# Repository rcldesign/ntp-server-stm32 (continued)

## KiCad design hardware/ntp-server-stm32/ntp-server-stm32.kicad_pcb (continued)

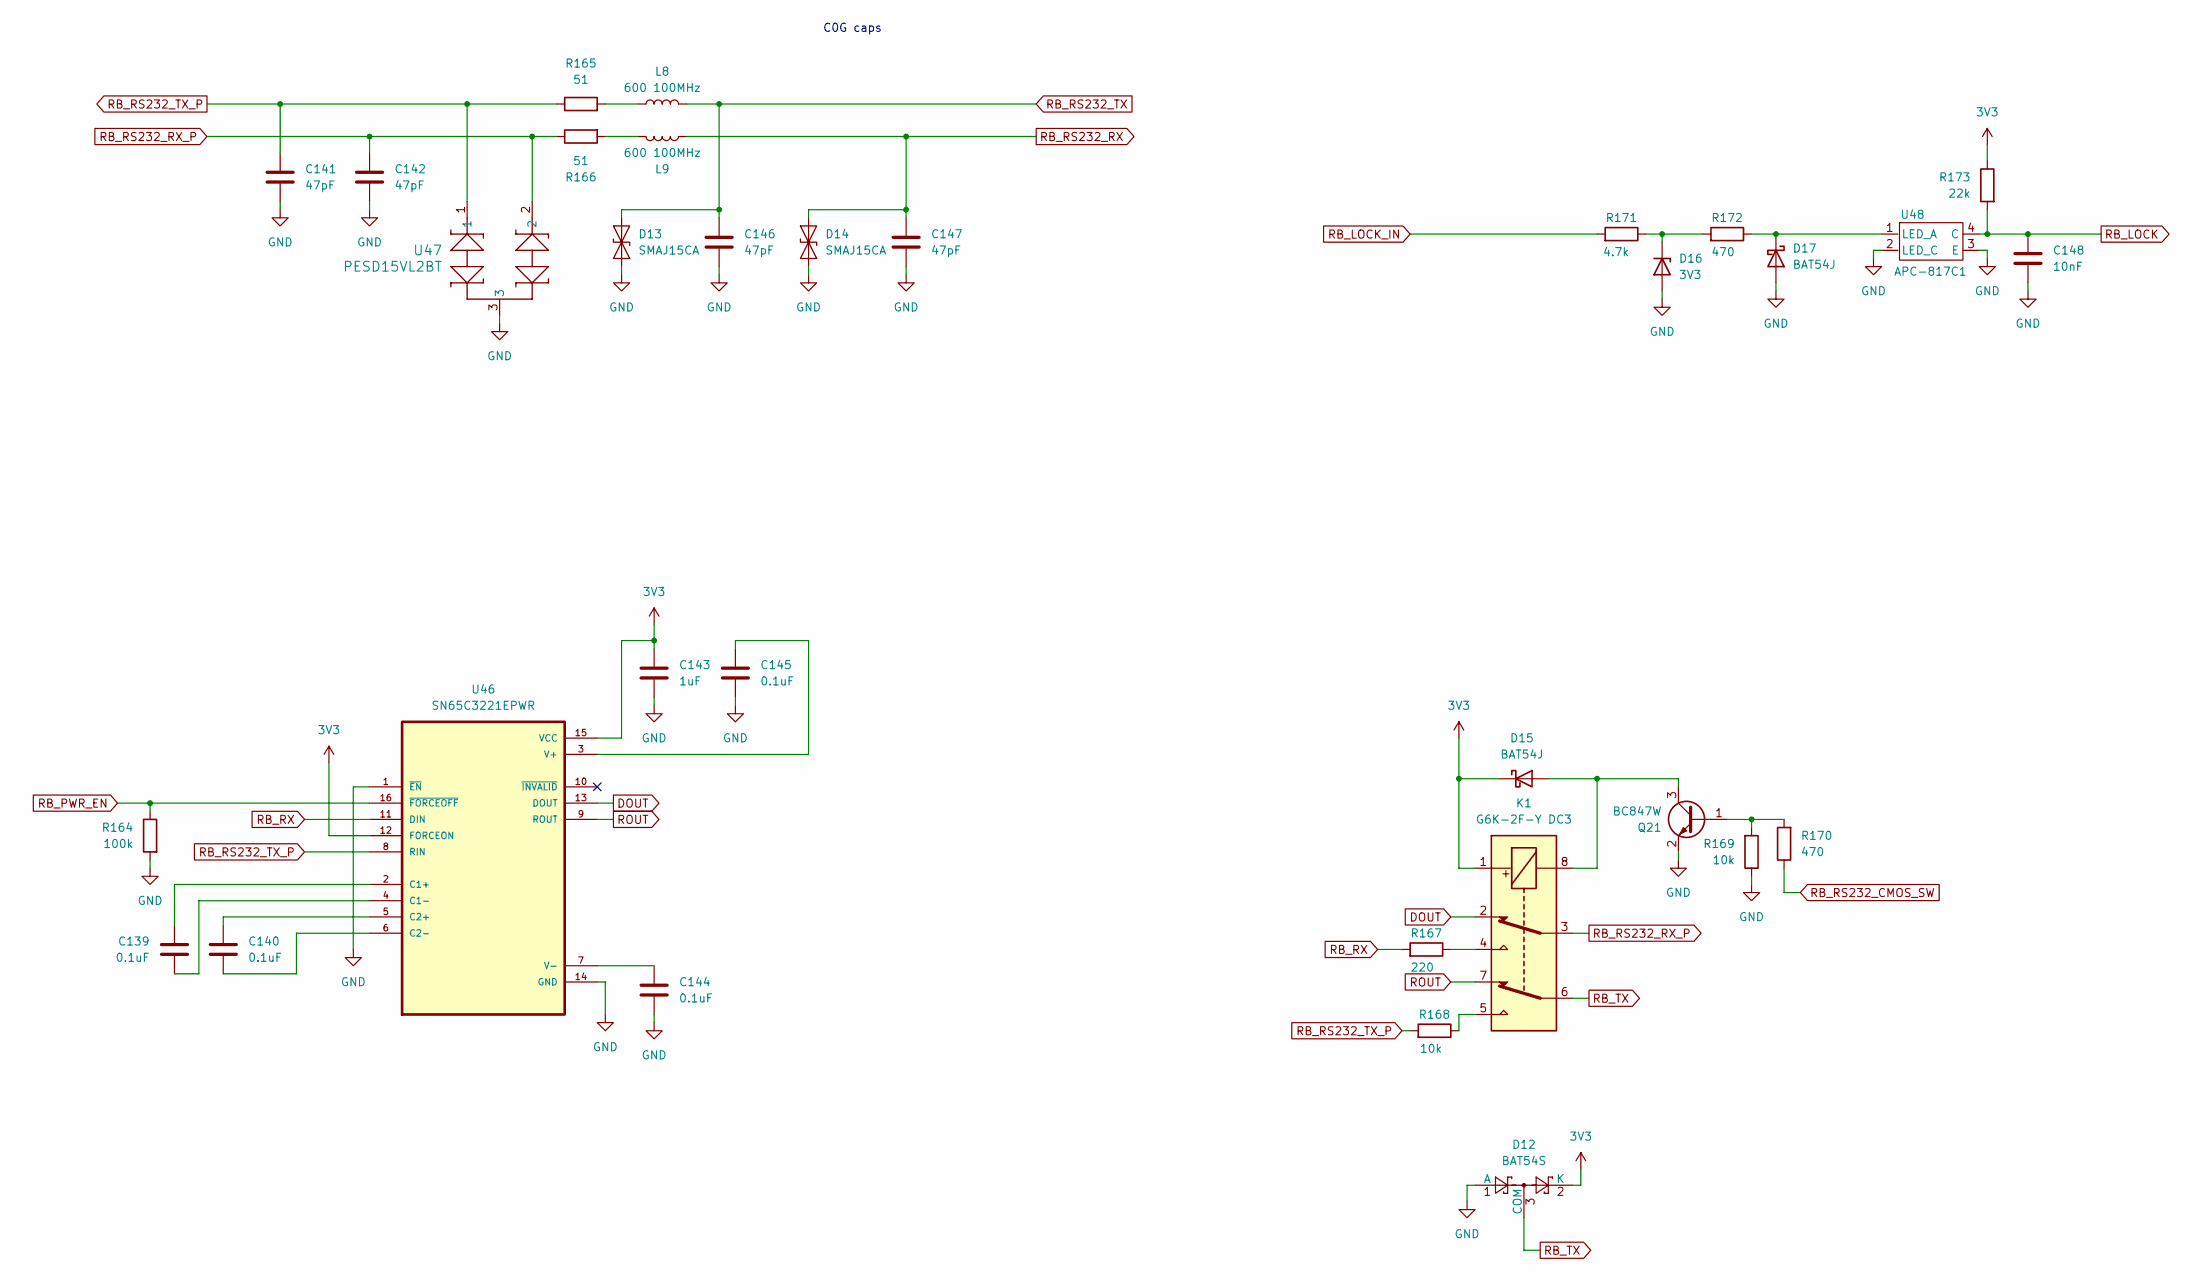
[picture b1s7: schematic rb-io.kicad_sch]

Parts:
C139, C140, C144, C145: 0.1uF; C_0402_1005Metric; TOLERANCE 10%; VOLTAGE 16V; MANUFACTURER_PART_NUMBER GCM155R71C104KA55D; DIGIKEY_PART_NUMBER 490-4759-1-ND
C141, C142, C146, C147: 47pF; C_0402_1005Metric; TOLERANCE 5%; VOLTAGE 50V; MANUFACTURER_PART_NUMBER GCM1555C1H470FA16D; DIGIKEY_PART_NUMBER 490-16445-1-ND
C143: 1uF; C_0603_1608Metric; TOLERANCE 10%; VOLTAGE 16V; MANUFACTURER_PART_NUMBER C0603C105K4RACAUTO; DIGIKEY_PART_NUMBER 399-17704-1-ND
C148: 10nF; C_0402_1005Metric; TOLERANCE 10%; VOLTAGE 16V; MANUFACTURER_PART_NUMBER GRT155R71C103KE01J; DIGIKEY_PART_NUMBER 490-GRT155R71C103KE01JCT-ND
D12: BAT54S; SOT-23-3; MANUFACTURER_PART_NUMBER BAT54S; DIGIKEY_PART_NUMBER 4878-BAT54SCT-ND
D13, D14: SMAJ15CA; DO-214AC; MANUFACTURER_PART_NUMBER SMAJ15CA; DIGIKEY_PART_NUMBER 732-SMAJ15CATR-ND
D15, D17: BAT54J; D_SOD-323F; MANUFACTURER_PART_NUMBER BAT54J-QX; DIGIKEY_PART_NUMBER 1727-BAT54J-QXCT-ND
D16: 3V3; SOT-23-3; MANUFACTURER_PART_NUMBER BZX84C3V3LT1G; DIGIKEY_PART_NUMBER BZX84C3V3LT1GOSCT-ND
K1: G6K-2F-Y DC3; MANUFACTURER_PART_NUMBER G6K-2F-Y DC3; DIGIKEY_PART_NUMBER 39-G6K-2F-YDC3-ND
L8, L9: 600 100MHz; L_0805_2012Metric; MANUFACTURER_PART_NUMBER 2508056017Y2; DIGIKEY_PART_NUMBER 1934-1487-2-ND
Q21: BC847W; SOT-323_SC-70; MANUFACTURER_PART_NUMBER BC847W,135; DIGIKEY_PART_NUMBER 1727-BC847W,135CT-ND
R164: 100k; R_0402_1005Metric; TOLERANCE 1%; MANUFACTURER_PART_NUMBER ERJ-2RKF1003X; DIGIKEY_PART_NUMBER P100KLCT-ND
R165, R166: 51; R_0402_1005Metric; TOLERANCE 1%; MANUFACTURER_PART_NUMBER ERJ-2RKF51R0X; DIGIKEY_PART_NUMBER P51.0LCT-ND
R167: 220; R_0402_1005Metric; TOLERANCE 1%; MANUFACTURER_PART_NUMBER ERJ-2RKF2200X; DIGIKEY_PART_NUMBER P220LCT-ND
R168, R169: 10k; R_0402_1005Metric; TOLERANCE 1%; MANUFACTURER_PART_NUMBER ERJ-2RKF1002X; DIGIKEY_PART_NUMBER P10.0KLCT-ND
R170, R172: 470; R_0402_1005Metric; TOLERANCE 1%; MANUFACTURER_PART_NUMBER ERJ-2RKF4700X; DIGIKEY_PART_NUMBER P470LCT-ND
R171: 4.7k; R_0402_1005Metric; TOLERANCE 1%; MANUFACTURER_PART_NUMBER ERJ-2RKF4701X; DIGIKEY_PART_NUMBER P4.70KLCT-ND
R173: 22k; R_0402_1005Metric; TOLERANCE 1%; MANUFACTURER_PART_NUMBER ERJ-2RKF2202X; DIGIKEY_PART_NUMBER P22.0KLCT-ND
U46: SN65C3221EPWR; SOP65P640X120-16N; MANUFACTURER_PART_NUMBER SN65C3221EPWR; DIGIKEY_PART_NUMBER 296-20992-1-ND
U47: PESD15VL2BT; TSOT-23; MANUFACTURER_PART_NUMBER PESD15VL2BT,215; DIGIKEY_PART_NUMBER 1727-3813-1-ND
U48: APC-817C1; APC817C1SL; MANUFACTURER_PART_NUMBER APC-817C1-SL; DIGIKEY_PART_NUMBER 2007-APC-817C1-SLCT-ND

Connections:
3V3: C143.1, D12.2 (K), D15.1 (K), K1.1, R173.1, U46.12 (FORCEON), U46.15 (VCC); also elsewhere on the board
DOUT: K1.2, U46.13 (DOUT)
GND: C141.2, C142.2, C143.2, C144.2, C145.2, C146.2, C147.2, C148.2, D12.1 (A), D13.1 (A1), D14.1 (A1), D16.2 (A), D17.2 (A), Q21.2 (E), R164.2, R169.1, U46.1 (~EN), U46.14 (GND), U47.3, U48.2 (LED_C), U48.3 (E); also elsewhere on the board
unnamed: D15.2 (A), K1.8, Q21.3 (C)
unnamed: D16.1 (K), R171.1, R172.2
unnamed: D17.1 (K), R172.1, U48.1 (LED_A)
unnamed: K1.4, R167.1
unnamed: K1.5, R168.1
unnamed: L8.1, R165.2
unnamed: L9.1, R166.2
unnamed: Q21.1 (B), R169.2, R170.2
unnamed: C139.1, U46.2 (C1+)
unnamed: C139.2, U46.4 (C1-)
unnamed: C140.1, U46.5 (C2+)
unnamed: C140.2, U46.6 (C2-)
unnamed: C145.1, U46.3 (V+)
unnamed: C144.1, U46.7 (V-)
RB_LOCK: C148.1, R173.2, U48.4 (C); also elsewhere on the board
RB_LOCK_IN: R171.2; also elsewhere on the board
RB_PWR_EN: R164.1, U46.16 (~FORCEOFF); also elsewhere on the board
RB_RS232_CMOS_SW: R170.1; also elsewhere on the board
RB_RS232_RX: C147.1, D14.2 (A2), L9.2; also elsewhere on the board
RB_RS232_RX_P: C142.1, K1.3, R166.1, U47.2
RB_RS232_TX: C146.1, D13.2 (A2), L8.2; also elsewhere on the board
RB_RS232_TX_P: C141.1, R165.1, R168.2, U46.8 (RIN), U47.1
RB_RX: R167.2, U46.11 (DIN); also elsewhere on the board
RB_TX: D12.3 (COM), K1.6; also elsewhere on the board
ROUT: K1.7, U46.9 (ROUT)

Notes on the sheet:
C0G caps

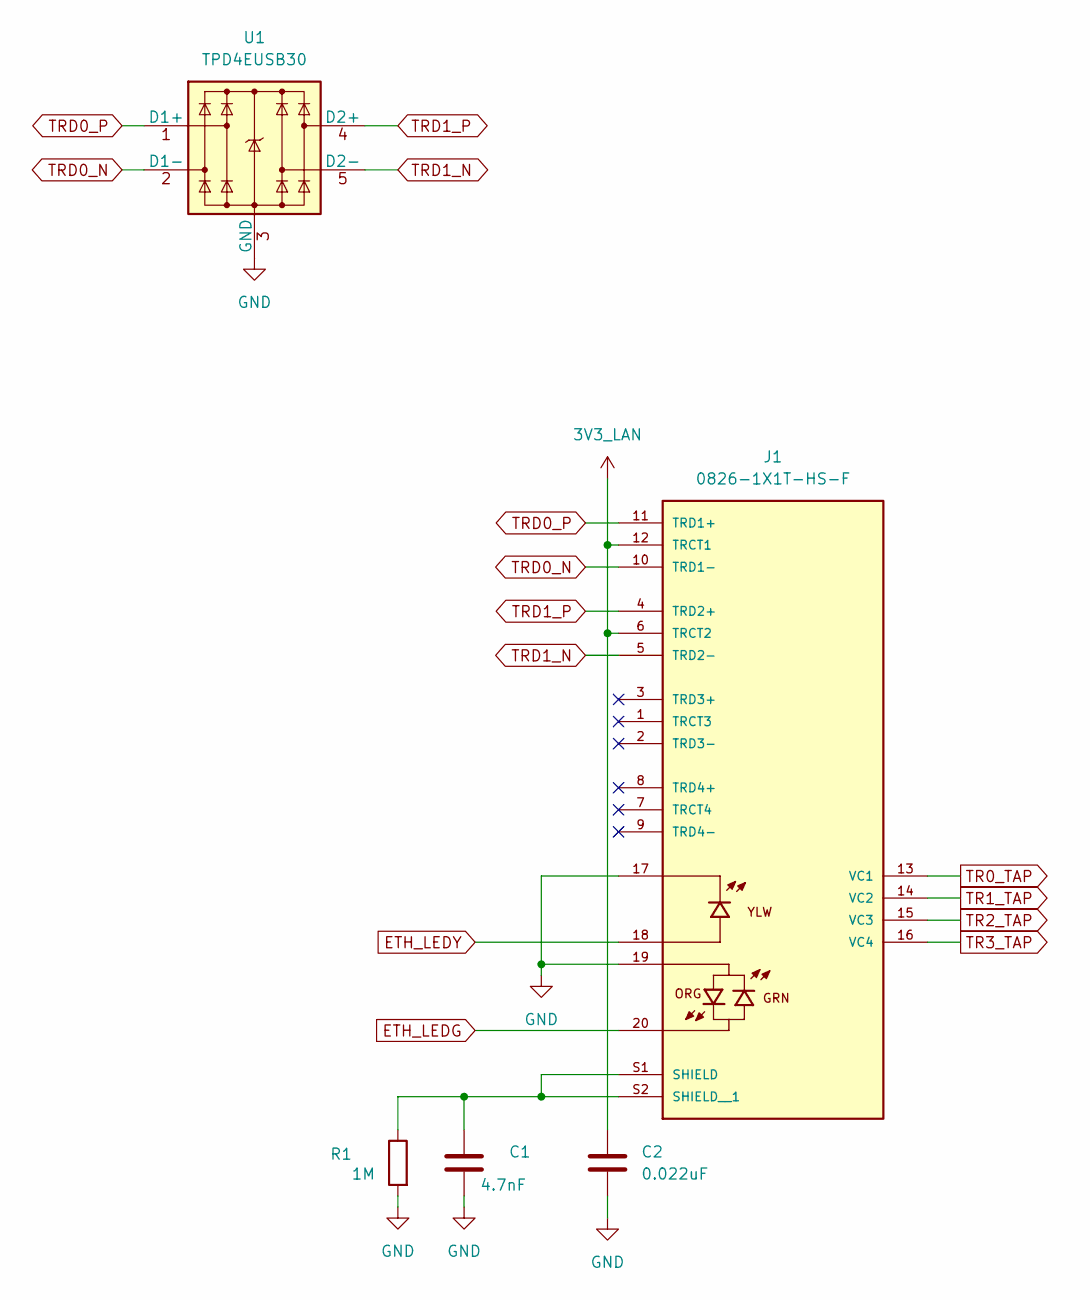
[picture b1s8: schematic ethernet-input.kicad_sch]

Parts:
C1: 4.7nF; C_1812_4532Metric; TOLERANCE 10%; VOLTAGE 2kV; MANUFACTURER_PART_NUMBER C1812C472KGRACAUTO; DIGIKEY_PART_NUMBER 399-16791-1-ND
C2: 0.022uF; C_0402_1005Metric; TOLERANCE 10%; VOLTAGE 50V; MANUFACTURER_PART_NUMBER C0402C223J5RACAUTO; DIGIKEY_PART_NUMBER 399-C0402C223J5RACAUTOCT-ND
J1: 0826-1X1T-HS-F; BEL_0826-1X1T-GH-F; PARTREV D; DIGIKEY_PART_NUMBER 507-2168-ND
R1: 1M; R_0402_1005Metric; TOLERANCE 1%; MANUFACTURER_PART_NUMBER ERJ-2RKF1004X; DIGIKEY_PART_NUMBER P1.00MLCT-ND
U1: TPD4EUSB30; TPD4E02B04DQAR; MANUFACTURER_PART_NUMBER TPD4EUSB30DQAR; DIGIKEY_PART_NUMBER 296-28063-1-ND

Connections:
3V3_LAN: C2.1, J1.6 (TRCT2), J1.12 (TRCT1); also elsewhere on the board
ETH_LEDG: J1.20; also elsewhere on the board
ETH_LEDY: J1.18; also elsewhere on the board
GND: C1.2, C2.2, J1.17, J1.19, R1.2, U1.3 (GND), U1.8 (GND); also elsewhere on the board
unnamed: C1.1, J1.S1 (SHIELD), J1.S2 (SHIELD__1), R1.1
TR0_TAP: J1.13 (VC1); also elsewhere on the board
TR1_TAP: J1.14 (VC2); also elsewhere on the board
TR2_TAP: J1.15 (VC3); also elsewhere on the board
TR3_TAP: J1.16 (VC4); also elsewhere on the board
TRD0_N: J1.10 (TRD1-), U1.2 (D1-), U1.9; also elsewhere on the board
TRD0_P: J1.11 (TRD1+), U1.1 (D1+), U1.10; also elsewhere on the board
TRD1_N: J1.5 (TRD2-), U1.5 (D2-), U1.6; also elsewhere on the board
TRD1_P: J1.4 (TRD2+), U1.4 (D2+), U1.7; also elsewhere on the board

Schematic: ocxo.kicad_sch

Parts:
C98, C99, C101: 0.1uF; C_1210_3225Metric; TOLERANCE 5%; VOLTAGE 16V; MANUFACTURER_PART_NUMBER C1210C104J5GACAUTO; DIGIKEY_PART_NUMBER 399-15804-1-ND
C100, C107, C118: 0.1uF; C_0402_1005Metric; TOLERANCE 10%; VOLTAGE 16V; MANUFACTURER_PART_NUMBER GCM155R71C104KA55D; DIGIKEY_PART_NUMBER 490-4759-1-ND
C102, C103, C104, C105, C111, C112, C113, C114, C115: 10uF; C_1206_3216Metric; TOLERANCE 10%; VOLTAGE 16V; MANUFACTURER_PART_NUMBER CL31B106KOHVPNE; DIGIKEY_PART_NUMBER 1276-6797-1-ND
C106, C110, C116: 10nF; C_0402_1005Metric; TOLERANCE 10%; VOLTAGE 16V; MANUFACTURER_PART_NUMBER GRT155R71C103KE01J; DIGIKEY_PART_NUMBER 490-GRT155R71C103KE01JCT-ND
C108: 4.7nF; C_0402_1005Metric; TOLERANCE 10%; VOLTAGE 16V; MANUFACTURER_PART_NUMBER C0402C472K4RECAUTO; DIGIKEY_PART_NUMBER 399-17875-1-ND
C109, C117: 22uF; C_0805_2012Metric; TOLERANCE 10%; VOLTAGE 16V; MANUFACTURER_PART_NUMBER GRT21BR61C226ME13K; DIGIKEY_PART_NUMBER 490-GRT21BR61C226ME13KCT-ND
D10: BAT54J; D_SOD-323F; MANUFACTURER_PART_NUMBER BAT54J-QX; DIGIKEY_PART_NUMBER 1727-BAT54J-QXCT-ND
L6: 2.2uH; DR73-2R2-R; MANUFACTURER_PART_NUMBER DR73-2R2-R; DIGIKEY_PART_NUMBER 283-DR73-2R2-RTR-ND
R118, R119, R120: 100k; R_0402_1005Metric; TOLERANCE 1%; MANUFACTURER_PART_NUMBER ERJ-2RKF1003X; DIGIKEY_PART_NUMBER P100KLCT-ND
R121: 10M; R_0402_1005Metric; TOLERANCE 1%; MANUFACTURER_PART_NUMBER RK73H1ETTP1005F; DIGIKEY_PART_NUMBER 2019-RK73H1ETTP1005FCT-ND
R122: 1k; R_0402_1005Metric; TOLERANCE 1%; MANUFACTURER_PART_NUMBER ERJ-2RKF1001X; DIGIKEY_PART_NUMBER P1.00KLCT-ND
R123: 22; R_0402_1005Metric; TOLERANCE 1%; MANUFACTURER_PART_NUMBER ERJ-2RKF22R0X; DIGIKEY_PART_NUMBER P22.0LCT-ND
R124, R131: 10k; R_0402_1005Metric; TOLERANCE 1%; MANUFACTURER_PART_NUMBER ERJ-2RKF1002X; DIGIKEY_PART_NUMBER P10.0KLCT-ND
R125: 3.57k; R_0402_1005Metric; TOLERANCE 1%; MANUFACTURER_PART_NUMBER ERJ-2RKF3571X; DIGIKEY_PART_NUMBER P3.57KLCT-ND
R126: 25m; R_1206_3216Metric; TOLERANCE 0.5%; MANUFACTURER_PART_NUMBER WSL1206R0250FEA; DIGIKEY_PART_NUMBER WSLC-.025CT-ND
R127: 12.4k; R_0402_1005Metric; TOLERANCE 1%; MANUFACTURER_PART_NUMBER ERJ-2RKF1242X; DIGIKEY_PART_NUMBER P12.4KLCT-ND
R128: 2.4k; R_0402_1005Metric; TOLERANCE 1%; MANUFACTURER_PART_NUMBER ERJ-2RKF2401X; DIGIKEY_PART_NUMBER P12.4KLCT-ND
R129: 12.1k; R_0603_1608Metric; TOLERANCE 0.1%; MANUFACTURER_PART_NUMBER RQ73C1J12K1BTD; DIGIKEY_PART_NUMBER A140146CT-ND
R130: 3.83k; R_0603_1608Metric; TOLERANCE 0.1%; MANUFACTURER_PART_NUMBER RQ73C1J3K83BTD; DIGIKEY_PART_NUMBER A140873CT-ND
U36: OPA320AIDBVT; SOT95P280X145-5N; MANUFACTURER_PART_NUMBER OPA320AIDBVT; DIGIKEY_PART_NUMBER 296-29510-1-ND
U37: INA228AQDGSRQ1; VSSOP10_DGS_TEX; MANUFACTURER_PART_NUMBER INA228AQDGSRQ1; DIGIKEY_PART_NUMBER 296-INA228AQDGSRQ1CT-ND
U38: AP3441SHE-7B; AP3441SHE-7B_DIO-M; MANUFACTURER_PART_NUMBER AP3441SHE-7B; DIGIKEY_PART_NUMBER AP3441SHE-7BDITR-ND
U39: TPS7A5201QRGRRQ1; RGR20_2P05X2P05_TEX; MANUFACTURER_PART_NUMBER TPS7A5201QRGRRQ1; DIGIKEY_PART_NUMBER 296-50505-1-ND
Y3: OH300; Oscillator_SMD_OCXO_ConnorWinfield_OH300; MANUFACTURER_PART_NUMBER OH300-61003CV-010.0M; DIGIKEY_PART_NUMBER CW752CT-ND

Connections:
3V3: C107.1, R131.1, U37.1 (A1), U37.6 (VS); also elsewhere on the board
5V: C102.1, C103.1, C104.1, U38.3 (VIN); also elsewhere on the board
5V_PSU_PG: U38.7 (EN); also elsewhere on the board
GND: C98.2, C99.2, C100.2, C101.2, C102.2, C103.2, C104.2, C105.2, C106.2, C107.2, C109.2, C111.2, C112.2, C113.2, C114.2, C115.2, C116.2, C117.2, C118.2, R119.1, R124.2, R128.2, R130.2, U36.2 (V-), U37.7 (GND), U38.4 (PGND), U38.8 (SGND), U38.9 (PAD), U39.8 (GND), U39.18 (GND), U39.21 (EPAD), Y3.7 (GND); also elsewhere on the board
I2C_SCL: U37.5 (SCL); also elsewhere on the board
I2C_SDA: U37.2 (A0), U37.4 (SDA); also elsewhere on the board
INA_ALERT_OCXO: U37.3 (ALERT); also elsewhere on the board
unnamed: C99.1, R118.2, R119.2, R121.1
unnamed: C109.1, C110.1, D10.2 (A), R126.2, R129.1, U37.10 (IN+), U39.1 (OUT), U39.19 (OUT), U39.20 (OUT)
unnamed: C108.1, C111.1, C112.1, C113.1, C114.1, C115.1, C117.1, C118.1, D10.1 (K), L6.2, R127.1, U39.12 (BIAS), U39.15 (IN), U39.16 (IN), U39.17 (IN)
unnamed: C98.1, R120.2, R121.2, U36.3 (+IN)
unnamed: R122.1, U36.1 (OUT), U36.4 (-IN)
unnamed: C105.1, C106.1, R126.1, U37.8 (VBUS), U37.9 (IN-), Y3.3 (VCC)
unnamed: C108.2, R127.2, R128.1, U38.1 (FB)
unnamed: L6.1, U38.6 (LX)
unnamed: R125.1, U38.2 (PG)
unnamed: C110.2, R129.2, R130.1, U39.3 (FB)
unnamed: C116.1, U39.13 (NR/SS)
unnamed: R123.1, Y3.4 (OUT)
OCXO_CLK_OUT: R123.2; also elsewhere on the board
OCXO_LDO_PG: R131.2, U39.4 (PG); also elsewhere on the board
OCXO_PSU_PG: R124.1, R125.2, U39.14 (EN); also elsewhere on the board
OCXO_V: C101.1, R122.2, Y3.1 (Vcontrol); also elsewhere on the board
OCXO_VC: R120.1; also elsewhere on the board
VDDA: C100.1, R118.1, U36.5 (V+); also elsewhere on the board

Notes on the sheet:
3.7V ->
<- 3.7V
PG pulled to VIN When power good
I2C Address: 0x46
50-ohm trace

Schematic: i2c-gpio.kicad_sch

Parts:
C161, C162, C163, C164, C165, C166, C167, C187, C202: 0.1uF; C_0402_1005Metric; TOLERANCE 10%; VOLTAGE 16V; MANUFACTURER_PART_NUMBER GCM155R71C104KA55D; DIGIKEY_PART_NUMBER 490-4759-1-ND
C201: 1nF; C_0402_1005Metric; TOLERANCE 5%; VOLTAGE 50V; MANUFACTURER_PART_NUMBER C0402C102J5GECAUTO; DIGIKEY_PART_NUMBER 399-C0402C102J5GECAUTOCT-ND
R190, R191, R192, R193, R194, R195, R196, R220, R221, R222, R223, R224, R225, R226, R227, R236, R254, R265: 10k; R_0402_1005Metric; TOLERANCE 1%; MANUFACTURER_PART_NUMBER ERJ-2RKF1002X; DIGIKEY_PART_NUMBER P10.0KLCT-ND

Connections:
3V3_STM: R190.1, R191.1, R192.1, R193.1, R194.1, R195.1, R196.1, R220.1, R221.1, R222.1, R223.1, R224.1, R225.1, R226.1, R227.1, R236.1, R254.1, R265.1; also elsewhere on the board
BUTTON_1: C161.1, R190.2; also elsewhere on the board
BUTTON_2: C162.1, R191.2; also elsewhere on the board
BUTTON_3: C163.1, R192.2; also elsewhere on the board
BUTTON_4: C164.1, R193.2; also elsewhere on the board
BUTTON_5: C165.1, R194.2; also elsewhere on the board
BUTTON_6: C166.1, R195.2; also elsewhere on the board
BUTTON_7: C167.1, R196.2; also elsewhere on the board
ENC_BUTTON: C187.1, R236.2; also elsewhere on the board
GND: C161.2, C162.2, C163.2, C164.2, C165.2, C166.2, C167.2, C187.2, C201.2, C202.2; also elsewhere on the board
INA_ALERT_3V3: R221.2; also elsewhere on the board
INA_ALERT_3V3_GPS: R224.2; also elsewhere on the board
INA_ALERT_3V3_STM: R222.2; also elsewhere on the board
INA_ALERT_5V_DISP: R223.2; also elsewhere on the board
INA_ALERT_5V_PANEL: R227.2; also elsewhere on the board
INA_ALERT_OCXO: R226.2; also elsewhere on the board
INA_ALERT_VCC_RB: R265.2; also elsewhere on the board
INA_ALERT_V_ANT: R225.2; also elsewhere on the board
INA_ALERT_V_POE: R220.2; also elsewhere on the board
PROX_WAKE: C202.1, R254.2; also elsewhere on the board
RTC_TAMPER: C201.1; also elsewhere on the board

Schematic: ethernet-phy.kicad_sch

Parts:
C13: 4.7uF; C_0805_2012Metric; TOLERANCE 10%; VOLTAGE 16V; MANUFACTURER_PART_NUMBER GRT21BR71C475KE13K; DIGIKEY_PART_NUMBER 490-GRT21BR71C475KE13KCT-ND
C14, C16: 27pF; C_0402_1005Metric; TOLERANCE 5%; VOLTAGE 50V; MANUFACTURER_PART_NUMBER GCM1555C1H270JA16D; DIGIKEY_PART_NUMBER 490-12651-1-ND
C15, C19, C20: 0.1uF; C_0402_1005Metric; TOLERANCE 10%; VOLTAGE 16V; MANUFACTURER_PART_NUMBER GCM155R71C104KA55D; DIGIKEY_PART_NUMBER 490-4759-1-ND
C17: 470pF; C_0402_1005Metric; TOLERANCE 5%; VOLTAGE 50V; MANUFACTURER_PART_NUMBER GCM1555C1H471FA16D; DIGIKEY_PART_NUMBER 490-GCM1555C1H471FA16DCT-ND
C18: 1uF; C_0603_1608Metric; TOLERANCE 10%; VOLTAGE 16V; MANUFACTURER_PART_NUMBER C0603C105K4RACAUTO; DIGIKEY_PART_NUMBER 399-17704-1-ND
FB1: 600; 1206; MANUFACTURER_PART_NUMBER BLM31PG601SN1L; DIGIKEY_PART_NUMBER 490-16533-1-ND
R31, R32, R33, R34: 100; R_0402_1005Metric; TOLERANCE 1%; MANUFACTURER_PART_NUMBER ERJ-2RKF1000X; DIGIKEY_PART_NUMBER P100LCT-ND
R35: 10k; R_0402_1005Metric; TOLERANCE 1%; MANUFACTURER_PART_NUMBER ERJ-2RKF1002X; DIGIKEY_PART_NUMBER P10.0KLCT-ND
R36: 1.5k; R_0402_1005Metric; TOLERANCE 1%; MANUFACTURER_PART_NUMBER ERJ-2RKF1501X; DIGIKEY_PART_NUMBER P1.50KLCT-ND
R37: 12.1k; R_0402_1005Metric; TOLERANCE 1%; MANUFACTURER_PART_NUMBER ERJ-2RKF1212X; DIGIKEY_PART_NUMBER P12.1KLCT-ND
R38, R39: 330; R_0402_1005Metric; TOLERANCE 1%; MANUFACTURER_PART_NUMBER ERJ-2RKF3300X; DIGIKEY_PART_NUMBER P330LCT-ND
R40, R41: 4.75k; R_0402_1005Metric; TOLERANCE 1%; MANUFACTURER_PART_NUMBER RK73H1ERTTP4751F; DIGIKEY_PART_NUMBER 2019-RK73H1ERTTP4751FCT-ND
R42, R43, R44, R45: 49.9; R_0402_1005Metric; TOLERANCE 1%; MANUFACTURER_PART_NUMBER ERJ-2RKF49R9X; DIGIKEY_PART_NUMBER P49.9LCT-ND
R49, R228, R229, R230: 4.99k; R_0402_1005Metric; TOLERANCE 1%; MANUFACTURER_PART_NUMBER ERJ-2RKF4991X; DIGIKEY_PART_NUMBER P4.99KLCT-ND
U11: LAN8742AI-CZ-TR; QFN50P400X400X100-25N; MANUFACTURER_PART_NUMBER LAN8742AI-CZ-TR; DIGIKEY_PART_NUMBER LAN8742AI-CZ-CT-ND
Y1: 25MHz; 445I23E25M00000; MANUFACTURER_PART_NUMBER 445I23E25M00000; DIGIKEY_PART_NUMBER 110-445I23E25M00000CT-ND

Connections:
3V3: C15.1, FB1.2, U11.9 (VDDIO); also elsewhere on the board
3V3_LAN: C13.1, C19.1, C20.1, FB1.1, R36.1, R42.1, R43.1, R44.1, R45.1, R49.1, R228.1, R229.1, U11.1 (VDD2A), U11.19 (VDD1A); also elsewhere on the board
ETH_LEDG: R38.2, R40.1; also elsewhere on the board
ETH_LEDY: R39.2, R41.1; also elsewhere on the board
GND: C13.2, C14.2, C15.2, C16.2, C17.2, C18.2, C19.2, C20.2, R35.2, R37.2, R40.2, R41.2, R230.2, U11.25 (VSS); also elsewhere on the board
LAN_RST_N: R35.1, U11.15 (~RST); also elsewhere on the board
unnamed: R33.2, R229.2, U11.11 (CRS_DV/MODE2)
unnamed: R38.1, U11.3 (LED1/~INT/~PME/REGOFF)
unnamed: R39.1, U11.2 (LED2/~INT/~PME/~INTSEL)
unnamed: R37.1, U11.24 (RBIAS)
unnamed: R31.2, R49.2, U11.8 (RXD0/MODE0)
unnamed: R32.2, R228.2, U11.7 (RXD1/MODE1)
unnamed: R34.2, R230.1, U11.10 (RXER/PHYAD0)
unnamed: C17.1, C18.1, U11.6 (VDDCR)
unnamed: C16.1, U11.5 (XTAL1/CLKIN), Y1.2
unnamed: C14.1, U11.4 (XTAL2), Y1.1
RMII_CRS_DV: R33.1; also elsewhere on the board
RMII_MDC: U11.13 (MDC); also elsewhere on the board
RMII_MDIO: R36.2, U11.12 (MDIO); also elsewhere on the board
RMII_REF_CLK: U11.14 (~INT/REFCLKO); also elsewhere on the board
RMII_RXD0: R31.1; also elsewhere on the board
RMII_RXD1: R32.1; also elsewhere on the board
RMII_RXER: R34.1; also elsewhere on the board
RMII_TXD0: U11.17 (TXD0); also elsewhere on the board
RMII_TXD1: U11.18 (TXD1); also elsewhere on the board
RMII_TX_EN: U11.16 (TXEN); also elsewhere on the board
TRD0_N: R44.2, U11.20 (TXN); also elsewhere on the board
TRD0_P: R45.2, U11.21 (TXP); also elsewhere on the board
TRD1_N: R42.2, U11.22 (RXN); also elsewhere on the board
TRD1_P: R43.2, U11.23 (RXP); also elsewhere on the board

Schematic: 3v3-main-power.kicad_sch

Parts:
C63: 10nF; C_0402_1005Metric; TOLERANCE 10%; VOLTAGE 16V; MANUFACTURER_PART_NUMBER GRT155R71C103KE01J; DIGIKEY_PART_NUMBER 490-GRT155R71C103KE01JCT-ND
C64, C65, C66, C73, C74, C76, C78: 10uF; C_1206_3216Metric; TOLERANCE 10%; VOLTAGE 16V; MANUFACTURER_PART_NUMBER CL31B106KOHVPNE; DIGIKEY_PART_NUMBER 1276-6797-1-ND
C67, C68, C83, C86, C87: 0.1uF; C_0402_1005Metric; TOLERANCE 10%; VOLTAGE 16V; MANUFACTURER_PART_NUMBER GCM155R71C104KA55D; DIGIKEY_PART_NUMBER 490-4759-1-ND
C69, C70: 4.7nF; C_0402_1005Metric; TOLERANCE 10%; VOLTAGE 16V; MANUFACTURER_PART_NUMBER C0402C472K4RECAUTO; DIGIKEY_PART_NUMBER 399-17875-1-ND
C71, C72: 47uF; C_1210_3225Metric; TOLERANCE 10%; VOLTAGE 16V; MANUFACTURER_PART_NUMBER GRT32EC81C476KE13L; DIGIKEY_PART_NUMBER 490-12494-1-ND
C75, C77, C80: 2.2uF; C_2220_5750Metric; TOLERANCE 10%; VOLTAGE 100V; MANUFACTURER_PART_NUMBER CGA9P3X7T2E225K250KA; DIGIKEY_PART_NUMBER 445-7950-1-ND
C79: 1uF; C_0805_2012Metric; TOLERANCE 10%; VOLTAGE 100V; MANUFACTURER_PART_NUMBER 08051C105K4T2A; DIGIKEY_PART_NUMBER 478-KAM21KR72A105KUCT-ND
C81: 4.7uF; C_0805_2012Metric; TOLERANCE 10%; VOLTAGE 16V; MANUFACTURER_PART_NUMBER GRT21BR71C475KE13K; DIGIKEY_PART_NUMBER 490-GRT21BR71C475KE13KCT-ND
C82: 2.2uF; C_0805_2012Metric; TOLERANCE 10%; VOLTAGE 16V; MANUFACTURER_PART_NUMBER GRT21BR71C225KE01L; DIGIKEY_PART_NUMBER 490-GRT21BR71C225KE01LCT-ND
C84, C85: 1uF; C_0603_1608Metric; TOLERANCE 10%; VOLTAGE 16V; MANUFACTURER_PART_NUMBER C0603C105K4RACAUTO; DIGIKEY_PART_NUMBER 399-17704-1-ND
FB7: 600; 1206; MANUFACTURER_PART_NUMBER BLM31PG601SN1L; DIGIKEY_PART_NUMBER 490-16533-1-ND
L2: 6.8uH; SRP1265A-6R8M; MANUFACTURER_PART_NUMBER SRP1265A-6R8M; DIGIKEY_PART_NUMBER SRP1265A-6R8MTR-ND
L3: 2.2uH; DR73-2R2-R; MANUFACTURER_PART_NUMBER DR73-2R2-R; DIGIKEY_PART_NUMBER 283-DR73-2R2-RTR-ND
R90: 200k; R_0402_1005Metric; TOLERANCE 1%; MANUFACTURER_PART_NUMBER ERJ-2RKF2003X; DIGIKEY_PART_NUMBER P200KLCT-ND
R91: 100k; R_0402_1005Metric; TOLERANCE 1%; MANUFACTURER_PART_NUMBER ERJ-2RKF1003X; DIGIKEY_PART_NUMBER P100KLCT-ND
R92, R95, R99, R104, R105: 10k; R_0402_1005Metric; TOLERANCE 1%; MANUFACTURER_PART_NUMBER ERJ-2RKF1002X; DIGIKEY_PART_NUMBER P10.0KLCT-ND
R93: 2.21k; R_0402_1005Metric; TOLERANCE 1%; MANUFACTURER_PART_NUMBER ERJ-2RKF2211X; DIGIKEY_PART_NUMBER P2.21KLCT-ND
R94: 6.81k; R_0402_1005Metric; TOLERANCE 1%; MANUFACTURER_PART_NUMBER ERJ-2RKF6811X; DIGIKEY_PART_NUMBER P6.81KLTR-ND
R96: 24.9k; R_0402_1005Metric; TOLERANCE 1%; MANUFACTURER_PART_NUMBER ERJ-2RKF2492X; DIGIKEY_PART_NUMBER P24.9KLCT-ND
R97: 15k; R_0402_1005Metric; TOLERANCE 1%; MANUFACTURER_PART_NUMBER RK73H1ETTP1502F; DIGIKEY_PART_NUMBER 2019-RK73H1ETTP1502FCT-ND
R98: 2.05k; R_0402_1005Metric; TOLERANCE 1%; MANUFACTURER_PART_NUMBER ERJ-2RKF2051X; DIGIKEY_PART_NUMBER P2.05KLTR-ND
R100: 2.2k; R_0402_1005Metric; TOLERANCE 1%; MANUFACTURER_PART_NUMBER ERJ-2RKF2201X; DIGIKEY_PART_NUMBER P2.20KLCT-ND
R101, R103: 2.2; R_0402_1005Metric; TOLERANCE 1%; MANUFACTURER_PART_NUMBER ERJ-U02F2R20X; DIGIKEY_PART_NUMBER 10-ERJ-U02F2R20XTR-ND
R102: 50m; R_1206_3216Metric; TOLERANCE 0.5%; MANUFACTURER_PART_NUMBER WSL1206R0500FEA; DIGIKEY_PART_NUMBER WSLC-.05CT-ND
R106, R107: 100m; R_1206_3216Metric; TOLERANCE 0.5%; MANUFACTURER_PART_NUMBER WSL1206R1000FEA; DIGIKEY_PART_NUMBER WSLC-.10CT-ND
U28: MIC28516T-E/PHA; MIC28516T-EPHA; MANUFACTURER_PART_NUMBER MIC28516T-E/PHA; DIGIKEY_PART_NUMBER 150-MIC28516T-E/PHATR-ND
U29: AP3441SHE-7B; AP3441SHE-7B_DIO-M; MANUFACTURER_PART_NUMBER AP3441SHE-7B; DIGIKEY_PART_NUMBER AP3441SHE-7BDITR-ND
U30, U31, U32: INA228AQDGSRQ1; VSSOP10_DGS_TEX; MANUFACTURER_PART_NUMBER INA228AQDGSRQ1; DIGIKEY_PART_NUMBER 296-INA228AQDGSRQ1CT-ND
U33: RT9742VGJ5; TSOT-23-5; MANUFACTURER_PART_NUMBER RT9742VGJ5; DIGIKEY_PART_NUMBER 1028-RT9742VGJ5TR-ND

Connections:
3V3: C83.1, C86.1, C87.1, R102.2, R106.1, U30.6 (VS), U30.8 (VBUS), U30.9 (IN-), U31.2 (A0), U31.6 (VS), U31.10 (IN+), U32.6 (VS); also elsewhere on the board
3V3_PSU_PG: R92.1, R94.2; also elsewhere on the board
3V3_STM: R105.1, R106.2, U31.8 (VBUS), U31.9 (IN-); also elsewhere on the board
5V: C64.1, C65.1, C66.1, C69.1, C71.1, C72.1, C84.1, L2.2, R95.1, R97.1, U29.3 (VIN), U33.5 (IN); also elsewhere on the board
5V_DISP: FB7.2; also elsewhere on the board
5V_PSU_PG: R95.2, U28.32 (PG), U29.7 (EN); also elsewhere on the board
DISP_EN: R104.1, U33.4 (EN); also elsewhere on the board
GND: C63.2, C64.2, C65.2, C66.2, C71.2, C72.2, C73.2, C74.2, C75.2, C76.2, C77.2, C78.2, C79.2, C80.2, C81.2, C82.2, C83.2, C84.2, C85.2, C86.2, C87.2, R91.2, R92.2, R98.2, R100.2, R104.2, U28.2 (PGND), U28.16 (PGND), U28.17 (PGND), U28.18 (PGND), U28.19 (PGND), U28.22 (PGND), U28.23 (EXTVDD), U28.28 (AGND), U28.29 (PGND), U28.33 (PGND), U29.4 (PGND), U29.8 (SGND), U29.9 (PAD), U30.1 (A1), U30.7 (GND), U31.1 (A1), U31.7 (GND), U32.1 (A1), U32.7 (GND), U33.2 (GND); also elsewhere on the board
I2C_SCL: U30.2 (A0), U30.5 (SCL), U31.5 (SCL), U32.5 (SCL); also elsewhere on the board
I2C_SDA: U30.4 (SDA), U31.4 (SDA), U32.2 (A0), U32.4 (SDA); also elsewhere on the board
INA_ALERT_3V3: U30.3 (ALERT); also elsewhere on the board
INA_ALERT_3V3_STM: U31.3 (ALERT); also elsewhere on the board
INA_ALERT_5V_DISP: U32.3 (ALERT); also elsewhere on the board
unnamed: C67.1, R96.2
unnamed: C68.2, L2.1, R93.2, R96.1, U28.3 (SW), U28.12 (SW), U28.13 (SW), U28.14 (SW), U28.15 (SW), U28.20 (SW)
unnamed: C68.1, U28.4 (BST)
unnamed: C67.2, C69.2, R97.2, R98.1, U28.27 (FB)
unnamed: R90.2, R91.1, U28.25 (FREQ)
unnamed: R93.1, U28.1 (ILIM)
unnamed: C63.1, U28.26 (SS)
unnamed: C81.1, R103.1, U28.21 (PVDD)
unnamed: C79.1, R101.2, U28.31 (SVIN)
unnamed: C82.1, R103.2, U28.30 (VDD)
unnamed: C70.2, R99.2, R100.1, U29.1 (FB)
unnamed: L3.1, U29.6 (LX)
unnamed: R94.1, U29.2 (PG)
unnamed: C70.1, C73.1, C74.1, C76.1, C78.1, L3.2, R99.1, R102.1, U30.10 (IN+)
unnamed: C85.1, R107.1, U32.10 (IN+), U33.1 (OUT)
unnamed: FB7.1, R107.2, U32.8 (VBUS), U32.9 (IN-)
POE_PG: U28.24 (EN); also elsewhere on the board
V_DISP_EN_FAULT: R105.2, U33.3 (nFLG); also elsewhere on the board
V_POE: C75.1, C77.1, C80.1, R90.1, R101.1, U28.5 (PVIN), U28.6 (PVIN), U28.7 (PVIN), U28.8 (PVIN), U28.9 (PVIN), U28.10 (PVIN), U28.11 (PVIN); also elsewhere on the board

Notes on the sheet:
I2C Address: 0x41
1.9A Maximum ->
PG pulled to VIN When power good
I2C Address: 0x42
I2C Address: 0x43
8A Maximum ->

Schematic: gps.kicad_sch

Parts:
C45, C47: 1uF; C_0603_1608Metric; TOLERANCE 10%; VOLTAGE 16V; MANUFACTURER_PART_NUMBER C0603C105K4RACAUTO; DIGIKEY_PART_NUMBER 399-17704-1-ND
C46: 4.7uF; C_0805_2012Metric; TOLERANCE 10%; VOLTAGE 16V; MANUFACTURER_PART_NUMBER GRT21BR71C475KE13K; DIGIKEY_PART_NUMBER 490-GRT21BR71C475KE13KCT-ND
C48, C51: 0.1uF; C_0402_1005Metric; TOLERANCE 10%; VOLTAGE 16V; MANUFACTURER_PART_NUMBER GCM155R71C104KA55D; DIGIKEY_PART_NUMBER 490-4759-1-ND
C49: 0.47uF; C_0603_1608Metric; TOLERANCE 10%; VOLTAGE 16V; MANUFACTURER_PART_NUMBER GRT188R71C474KE01D; DIGIKEY_PART_NUMBER 490-GRT188R71C474KE01DCT-ND
C50: 10uF; C_1206_3216Metric; TOLERANCE 10%; VOLTAGE 16V; MANUFACTURER_PART_NUMBER CL31B106KOHVPNE; DIGIKEY_PART_NUMBER 1276-6797-1-ND
FB3: 600; 1206; MANUFACTURER_PART_NUMBER BLM31PG601SN1L; DIGIKEY_PART_NUMBER 490-16533-1-ND
R69: 100k; R_0402_1005Metric; TOLERANCE 1%; MANUFACTURER_PART_NUMBER ERJ-2RKF1003X; DIGIKEY_PART_NUMBER P100KLCT-ND
R70: 374; R_0402_1005Metric; TOLERANCE 1%; MANUFACTURER_PART_NUMBER ERJ-2RKF3740X; DIGIKEY_PART_NUMBER P374LCT-ND
R71: 33.2k; R_0402_1005Metric; TOLERANCE 1%; MANUFACTURER_PART_NUMBER ERJ-2RKF3322X; DIGIKEY_PART_NUMBER P33.2KLCT-ND
R72: 75m; R_1206_3216Metric; TOLERANCE 0.5%; MANUFACTURER_PART_NUMBER WSL1206R0750FEA; DIGIKEY_PART_NUMBER 541-10064-1-ND
R197: 453k; R_0402_1005Metric; TOLERANCE 1%; MANUFACTURER_PART_NUMBER ERJ-2RKF4533X; DIGIKEY_PART_NUMBER P453KLCT-ND
R214: 49.9k; R_0402_1005Metric; TOLERANCE 1%; MANUFACTURER_PART_NUMBER ERJ-2RKF4992X; DIGIKEY_PART_NUMBER P49.9KLCT-ND
R215: 10k; R_0402_1005Metric; TOLERANCE 1%; MANUFACTURER_PART_NUMBER ERJ-2RKF1002X; DIGIKEY_PART_NUMBER P10.0KLCT-ND
U21: ZED-F9T-00B; MODULE_ZED-F9T-00B; MANUFACTURER_PART_NUMBER ZED-F9T-00B; DIGIKEY_PART_NUMBER 672-1197-1-ND
U22: LT3045xDD; DFN-10-1EP_3x3mm_P0.5mm_EP1.65x2.38mm; MANUFACTURER_PART_NUMBER LT3045EDD#TRPBF; DIGIKEY_PART_NUMBER 505-LT3045EDD#TRPBFCT-ND
U23: INA228AQDGSRQ1; VSSOP10_DGS_TEX; MANUFACTURER_PART_NUMBER INA228AQDGSRQ1; DIGIKEY_PART_NUMBER 296-INA228AQDGSRQ1CT-ND

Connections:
3V3: C51.1, U23.6 (VS); also elsewhere on the board
3V3_GPS: C45.1, C47.1, R72.2, U21.33 (VCC), U21.34 (VCC__1), U23.8 (VBUS), U23.9 (IN-); also elsewhere on the board
3V3_GPS_LDO_PG: R215.2, U22.4 (PG); also elsewhere on the board
3V3_STM: R215.1; also elsewhere on the board
5V: FB3.2; also elsewhere on the board
GND: C45.2, C46.2, C47.2, C48.2, C49.2, C50.2, C51.2, R69.2, R70.2, R71.2, R214.2, U21.1 (GND1), U21.3 (GND1__1), U21.12 (GND1__2), U21.14 (GND1__3), U21.32 (GND1__4), U21.37 (GND1__5), U21.38 (V_USB), U21.41 (GND1__6), U21.48 (GND1__7), U21.55 (GND1__8), U21.56 (GND1__9), U21.57 (GND1__10), U21.58 (GND1__11), U21.59 (GND1__12), U21.60 (GND1__13), U21.61 (GND1__14), U21.62 (GND2), U21.63 (GND2__1), U21.64 (GND2__2), U21.65 (GND2__3), U21.66 (GND2__4), U21.67 (GND2__5), U21.68 (GND2__6), U21.69 (GND2__7), U21.70 (GND2__8), U21.71 (GND2__9), U21.72 (GND2__10), U21.73 (GND2__11), U21.74 (GND2__12), U21.75 (GND2__13), U21.76 (GND2__14), U21.77 (GND3), U21.78 (GND3__1), U21.79 (GND3__2), U21.80 (GND3__3), U21.81 (GND3__4), U21.82 (GND3__5), U21.83 (GND3__6), U21.84 (GND3__7), U21.85 (GND3__8), U21.86 (GND3__9), U21.87 (GND3__10), U21.88 (GND3__11), U21.89 (GND3__12), U21.90 (GND3__13), U21.91 (GND3__14), U21.92 (GND4), U21.93 (GND4__1), U21.94 (GND4__2), U21.95 (GND4__3), U21.96 (GND4__4), U21.97 (GND4__5), U21.98 (GND4__6), U21.99 (GND4__7), U21.100 (GND4__8), U21.101 (GND4__9), U21.102 (GND4__10), U22.8 (GND), U22.11 (GND), U23.7 (GND); also elsewhere on the board
GPS_ANT_DETECT: U21.4 (ANT_DETECT); also elsewhere on the board
GPS_ANT_OFF_MON: U21.5 (ANT_OFF); also elsewhere on the board
GPS_ANT_SHORT: U21.6 (~ANT_SHORT); also elsewhere on the board
GPS_DSEL: U21.47 (D_SEL); also elsewhere on the board
GPS_EXTINT: U21.51 (EXTINT); also elsewhere on the board
GPS_PPS: U21.53 (TIMEPULSE); also elsewhere on the board
GPS_PWR_EN: R69.1, U22.3 (EN/UV); also elsewhere on the board
GPS_RF_IN: U21.2 (RF_IN); also elsewhere on the board
GPS_RST_N: U21.49 (~RESET); also elsewhere on the board
GPS_RX: U21.43 (RXD/SPI_SDI); also elsewhere on the board
GPS_RXD2: U21.26 (RXD2); also elsewhere on the board
GPS_SAFEBOOT_N: U21.50 (~SAFEBOOT); also elsewhere on the board
GPS_TP2: U21.54 (TIMEPULSE2); also elsewhere on the board
GPS_TX: U21.42 (TXD/SPI_SDO); also elsewhere on the board
GPS_TXD2: U21.27 (TXD2); also elsewhere on the board
GPS_TXRDY: U21.19 (GEOFENCE_STAT); also elsewhere on the board
GPS_VBAT: C48.1, U21.36 (V_BCKP); also elsewhere on the board
I2C_SCL: U23.5 (SCL); also elsewhere on the board
I2C_SDA: U23.1 (A1), U23.2 (A0), U23.4 (SDA); also elsewhere on the board
INA_ALERT_3V3_GPS: U23.3 (ALERT); also elsewhere on the board
unnamed: C46.1, FB3.1, U22.1 (IN), U22.2 (IN)
unnamed: R70.1, U22.5 (ILIM)
unnamed: C50.1, R72.1, R197.1, U22.9 (OUTS), U22.10 (OUT), U23.10 (IN+)
unnamed: R197.2, R214.1, U22.6 (PGFB)
unnamed: C49.1, R71.1, U22.7 (SET)

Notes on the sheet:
Place close to power pins
Noise Sensitive See Datasheet for Layout
I2C Address: 0x4A
